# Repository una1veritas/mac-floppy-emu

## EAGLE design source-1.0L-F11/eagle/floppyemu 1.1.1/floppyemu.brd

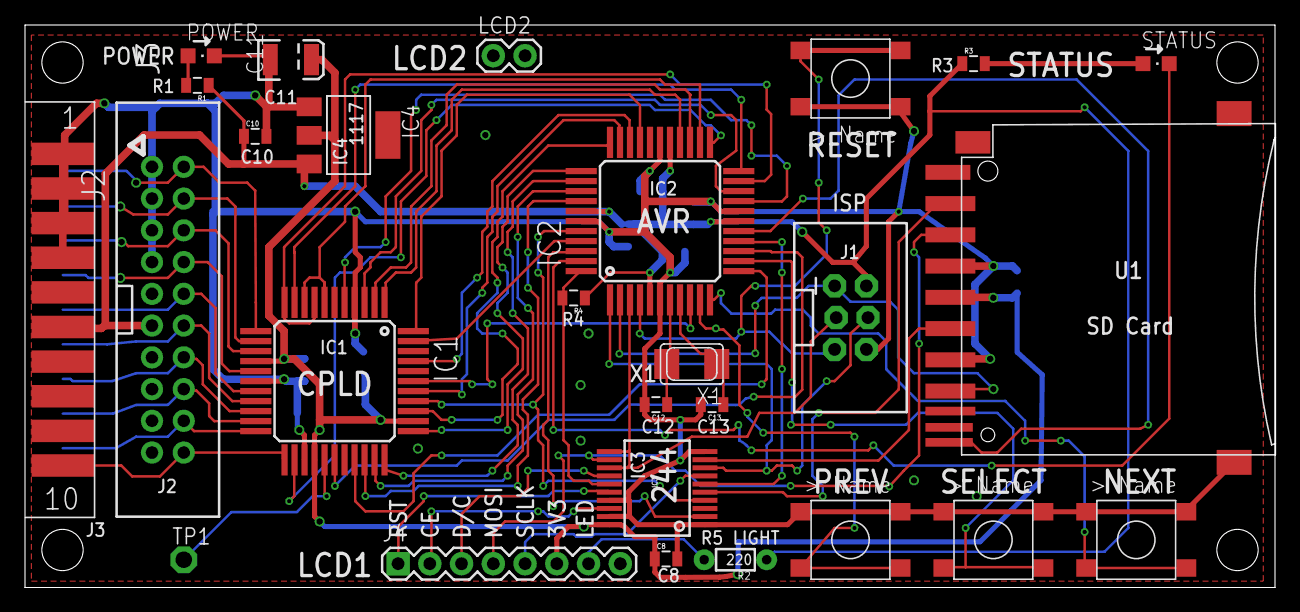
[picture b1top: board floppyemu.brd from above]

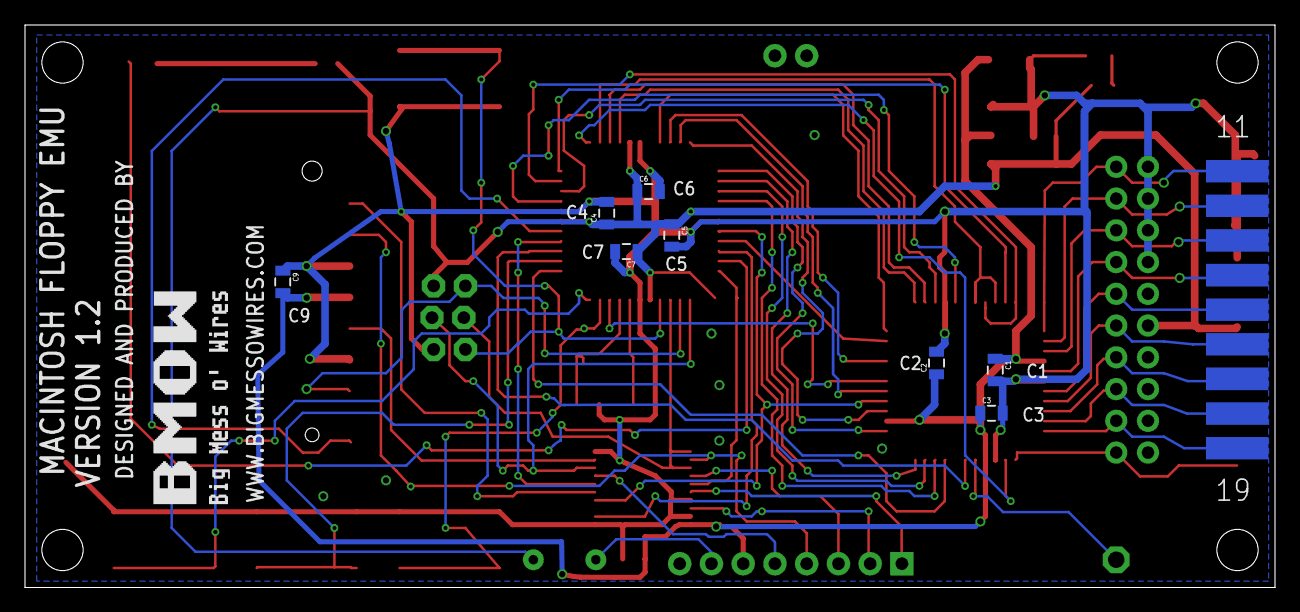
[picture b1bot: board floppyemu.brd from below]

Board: 2 copper layers, 100.0 x 45.0 mm, 39 parts (8 on the bottom side), 59 nets.

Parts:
C1, C2, C3, C4, C5, C6, C7, C8, C9, C10: 0.1uF; 0805
C11: 33uF; EIA3528
C12, C13: 18pF; 0805
IC1: XC9572XLTQFP44; TQFP44-LONGPADS
IC2: BIG-MESS-O-WIRES_ATMEGA1284; BIG-MESS-O-WIRES_TQFP44-LONGPADS
IC3: 74LVC244; SSOP20
IC4: REG1117; SOT223
J1: BIG-MESS-O-WIRES_AVR_ISP; BIG-MESS-O-WIRES_2X3-SHROUDED
J2: IDC20
J3: DB19; DB19EDGE
J4: LCD1; 1X08
LCD2: M02PTH; 1X02
NEXT: B3FS-10XX; B3FS
POWER: CHIPLED_0805
PREV: B3FS-10XX; B3FS
R1, R3: 220R; 0805
R2: 220; 1/6W-RES
R4: 10K; 0805
RESET: B3FS-10XX; B3FS
SELECT: B3FS-10XX; B3FS
STANDOFF1, STANDOFF2, STANDOFF3, STANDOFF4: STAND-OFF
STATUS: CHIPLED_0805
TP1: PTR1PAD1-13; P1-13
U1: ADAFRUIT_SDMMC06132; ADAFRUIT_06132
X1: 20 MHz; NX5032

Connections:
+3V3: C1.1, C2.1, C3.1, C8.1, C9.2, C11.A, IC1.15, IC1.26, IC1.35, IC3.20, IC4.2, J4.6, U1.4
+5V: C4.1, C5.1, C6.1, C7.1, C10.1, IC2.5, IC2.17, IC2.27, IC2.38, IC4.3, J1.2, J2.11, J3.6, R1.1, R2.1, R3.1, R4.1
/ENBL.EXT: IC1.20, J2.14, J3.17
/WREQ: IC1.18, J2.10, J3.15
/WREQM: IC1.5, IC2.19
BYTER/TDI: IC1.7, IC1.9, IC2.24
CLKO: IC1.43, IC2.41
D0: IC1.31, IC2.37
D1: IC1.32, IC2.36
D2: IC1.33, IC2.35
D3: IC1.34, IC2.34
D4: IC1.36, IC2.33
D5: IC1.38, IC2.32
D6: IC1.41, IC2.31
DC: IC2.15, IC3.6
DC33: IC3.14, J4.3
DIN/STA/TCK: IC1.8, IC1.11, IC2.21
EJECT: IC1.30, IC2.12
GND: C1.2, C2.2, C3.2, C4.2, C5.2, C6.2, C7.2, C8.2, C9.1, C10.2, C11.C, C12.2, C13.2, IC1.4, IC1.17, IC1.25, IC2.6, IC2.18, IC2.28, IC2.39, IC3.1, IC3.10, IC3.17, IC3.19, IC4.1, J1.6, J2.1, J2.3, J2.5, J2.7, J3.1, J3.2, J3.3, J3.4, J4.8, NEXT.A, NEXT.A', POWER.C, PREV.A, PREV.A', RESET.A, RESET.A', SELECT.A, SELECT.A', U1.3, U1.6, U1.GP
LCDE: IC2.42, IC3.2
LCDE33: IC3.18, J4.2
LEDD: IC2.43, STATUS.C
MISO: IC2.2, J1.1, U1.7
MOSI: IC2.1, IC3.8, J1.4
MOSI33: IC3.12, J4.4, U1.2
unnamed: C13.1, IC2.8, X1.P$2
unnamed: POWER.A, R1.2
unnamed: C12.1, IC2.7, X1.P$1
unnamed: R3.2, STATUS.A
unnamed: J4.7, R2.2
NEXT: IC2.11, NEXT.B, NEXT.B'
OE: IC1.2, IC2.25
PH0: IC1.12, J2.2, J3.11
PH1: IC1.13, J2.4, J3.12
PH2: IC1.14, J2.6, J3.13
PH3: IC1.16, J2.8, J3.14
PREV: IC2.10, PREV.B, PREV.B'
PWM: IC1.23, J2.20, J3.10
RD: IC1.21, J2.16, J3.18
RDAWRT: IC1.44, IC2.30
RESET: IC2.4, J1.5, RESET.B, RESET.B'
RST: IC1.37, IC2.40, IC3.4
RST33: IC3.16, J4.1
SCK: IC2.3, IC3.11, IC3.13, J1.3
SCK33: IC3.9, U1.5
SCK33A: IC3.7, J4.5
SDE: IC2.44, IC3.15, R4.2
SDE33: IC3.5, U1.1
SEL: IC1.19, J2.12, J3.16
SELECT: IC2.13, SELECT.B, SELECT.B'
SIDE: IC1.3, IC2.20
STPDIR_MOTOR: IC1.1, IC2.26
STPREQ: IC1.39, IC2.9
TACH: IC1.28, IC2.14
TDO: IC1.24, IC2.23
TEST: IC1.27, TP1.TP
TMS: IC1.10, IC2.22
WPROT: IC2.16, U1.WP
WR: IC1.22, J2.18, J3.19

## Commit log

2014-07-10 My first
2014-07-10 ignore file
2014-07-10 Eclipse compilation
2014-07-10 floppy-emu
2014-07-12 floppy-emu organized
2014-07-12 arduino
2014-07-14 source
2014-07-14 floppyemu/floppy_emu_arduino
2014-07-15 floppy emu

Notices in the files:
parts and their libraries:
SparkFun-Connectors: Licensing: CC v3.0 Share-Alike You are welcome to use this library for commercial purposes.
